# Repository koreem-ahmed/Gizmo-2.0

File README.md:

# Gizmo 2.0
## Description
Gizmo 2.0 is generally a small desk robot that acts as an AI companion whose only mission is to interact with you, dance with you, and even brainstorm with you. Gizmo 2.0 can help you organize your thoughts, and he gives incredible answers for any questions you ask him. Also, he is provided with a mic for voice and music recognition. So, you can have a little party with him, and it has 2 servo motors that act as joints for his arms, which are mainly used for dancing and interaction with his owner.

Gizmo was made after a lot of research and thinking i had like a really long time seeing totorial and example on the internet to see how to make a moving AI companian and which MCU to get and what could be its abailities so i used ESP32-S3 as the main MCU, inmp441 as a microphone, a speaker, 2 servo motors and a customed PCB to hold every thing together.

## Why it was biult
I had a really good time designing Gizmo as I made a unique 3D design with inspiration from EVE in the Wall-E robot film. As a kid I loved this character so much, and since it was really quiet and charming, it was like a new technology on earth to clean the planet, but I made it a little different. I made it to be like a moving thing on my desk to dance with me and interact with me when having long programming or designing sessions. Gizmo will be there for you. I wanted to make it with a moving wheels but i couldn't get a good design as well as that my desk is not that big for a moving robot So i ended up by making a static one with moving arms and a big processer which is the ESP32-S3.

There is another good reaseon for building Gizmo which is the amount of memories and thoughsts i gave into biulding it. Since this is my last project before attendign fallout which is a hackathon organized by Hack Club in shenzhen and i can't wait to go.

## How to use it / Build it
The first step of constructing Gizmo 2.0 is fabricating the PCB since it will be one of the main parts of the prototype. Also, you need it since the prototype doesn't have any additional space to maintain the electronics without the PCB. So, after fabricating the PCB, you should buy the components as well as jumpers and long wires for the LCD, speaker, and servo motors. After that you should 3D print the parts I provided in the repo, and for each part there is a compatible part in the main body, which will hold everything from servo motors to the connector and the head, which is part 5 or head connector; this connects to the neck of the head part.

Now we start the assembly. First of all, get your LCD and glue it to the front head part, then glue the speaker to the back head part, and assemble the 2 parts using the neck I provided, which has a place to hold all these parts together. After this, get the base and add the PCB after assembling everything and uploading the firmware. and close the base with the top part of the base and then assemble the main body and the servo motor holder and glue the servo motors to the part, then glue the arm to the servo motor after it to the main body after assembling the arms to the body. Now you have a full working prototype.

## CAD
I made this 3D design using onshape software, it was like a new experience for me to design a small prototype like a robot with this components so i had a new experience and i made every thing with smth like joints to hold it together. Also i added my name and HC for Hack Club.
And this is the design link:
https://cad.onshape.com/documents/7c9149f39106583a98e32532/w/5ca8de735c404b6ef83d1411/e/55ea2a7bab61e22144a448e0?renderMode=0&uiState=6a34a954f7594a7258307f8a
<br>

## Schematic
This is a simple diagram for my circiut it havethenamea small introduction a digra for whot will the system work and 2 systems the power and the ESP32-S3 connections

## PCB design
A polished PCB design with a copper filled zone to my GND net also i assimblied it many times until i got this one with no problems.

## Magazine

## BOM

| Item | Price | Quan. | Place | Link |
| :--- | :---: | :---: | :--- | :--- |
| ESP32-s3 | 10.55 | 1 | future electronics | [View Item](https://store.fut-electronics.com/products/esp32-s3-devkitc-1?srsltid=AfmBOoo5ok_RH336v4kgNkFmU0aAF1dDe45BG5KH02IJx1Rra65h0LNp) |
| ESP32 Camera OV5640 | 7.58 | 1 | makers | [View Item](https://makerselectronics.com/product/banana-pi-camera-ov5640-160-degree-5mp/?srsltid=AfmBOoqwwII_0DwU1h8Btitem8w31jUf-n4unO7NtXqaaZ5AVWlHgDsY) |
| 18650 Lithium Ion Rechargeable | 4.62 | 2 | future electronics | [View Item](https://fut-electronics.com) |
| AMS1117 3.3V Step-Down | 1 | 1 | micro ohm | [View Item](https://microohm-eg.com/ams1117-3-3-ldo-800ma-dc-5v-to-3-3v-step-down-power-supply-module/) |
| Step Down 5A XL4015 | 1.63 | 1 | micro ohm | [View Item](https://microohm-eg.com/dc-dc-step-down-converter-variable-5a-xl4015/) |
| BMS 2S 13A Lithium Battery Protection Board | 1.5 | 1 | micro ohm | [View Item](https://microohm-eg.com/2s-13a-18650-7-4v-8-4v-lithium-battery-protection-board/?utm_source=chatgpt.com) |
| 2S 8.4V 2A 18650 Lithium Battery Charger Module USB Type C | | 1 | ram electronics | [View Item](https://www.ram-e-shop.com/ar/shop/kit-li-2s-charger-2s-8-4v-2a-18650-lithium-battery-charger-module-usb-type-c-9295?srsltid=AfmBOoqNP3OFFPA_uS9me429NkSkgtTsNjoG1qEyEM67Y3l1D3-WlItv) |
| inm441 | 5.25 | 1 | Ali express | [View Item](https://ar.aliexpress.com/item/32934187800.html?gatewayAdapt=glo2ara) |
| i2s amplifier (max 98357) | 2.6 | 1 | future electronics | [View Item](https://store.fut-electronics.com/products/max98357-i2s-3w-class-d-amplifier-audio-decoder-module?srsltid=AfmBOoqAc6RcUHtToGTEkW9skKCJ9fX_xuc7YFtfUabfdsT7n0q2HLyD) |
| Speaker - 3W 4 Ohm | 1.54 | 1 | future electronics | [View Item](https://store.fut-electronics.com/products/speaker-3w-4-ohm?srsltid=AfmBOopv4otZbRL29DhJ3REfWfF-85G6EDgruAXGc6kVUNDOp2_l61lA) |
| LCD Module 1.28 inch Round Display | 9 | 1 | micro ohm | [View Item](https://microohm-eg.com/round-lcd-module-1-28-inch-240x240-ips-color-with-gc9a01-controller/) |
| TTP223 Capacitive Touch Sensor | 0.29 | 2 | makers | [View Item](https://makerselectronics.com/product/ttp223-capacitive-touch-sensor-module/?srsltid=AfmBOop7F_AzNeOoilzYLkXKq8DPKwVegbdnGAW85MecGYuK8TcNj0Ez) |
| 1.3 kg.cm servo | 2 | 2 | Circuits electronics | [View Item](https://circuits-elec.com/products/servo-motor-1-3-kg-cm-standard?srsltid=AfmBOoorhdeY6_q4NXN0ngcBwieEeBY9QWrYb_PrgZwciAxm65uJPD-Y) |
| PCB fabrication | 5 | 1 | JLCPCB | |
| 3D design | 20 | | | |
| **Total** | **75** | | | |

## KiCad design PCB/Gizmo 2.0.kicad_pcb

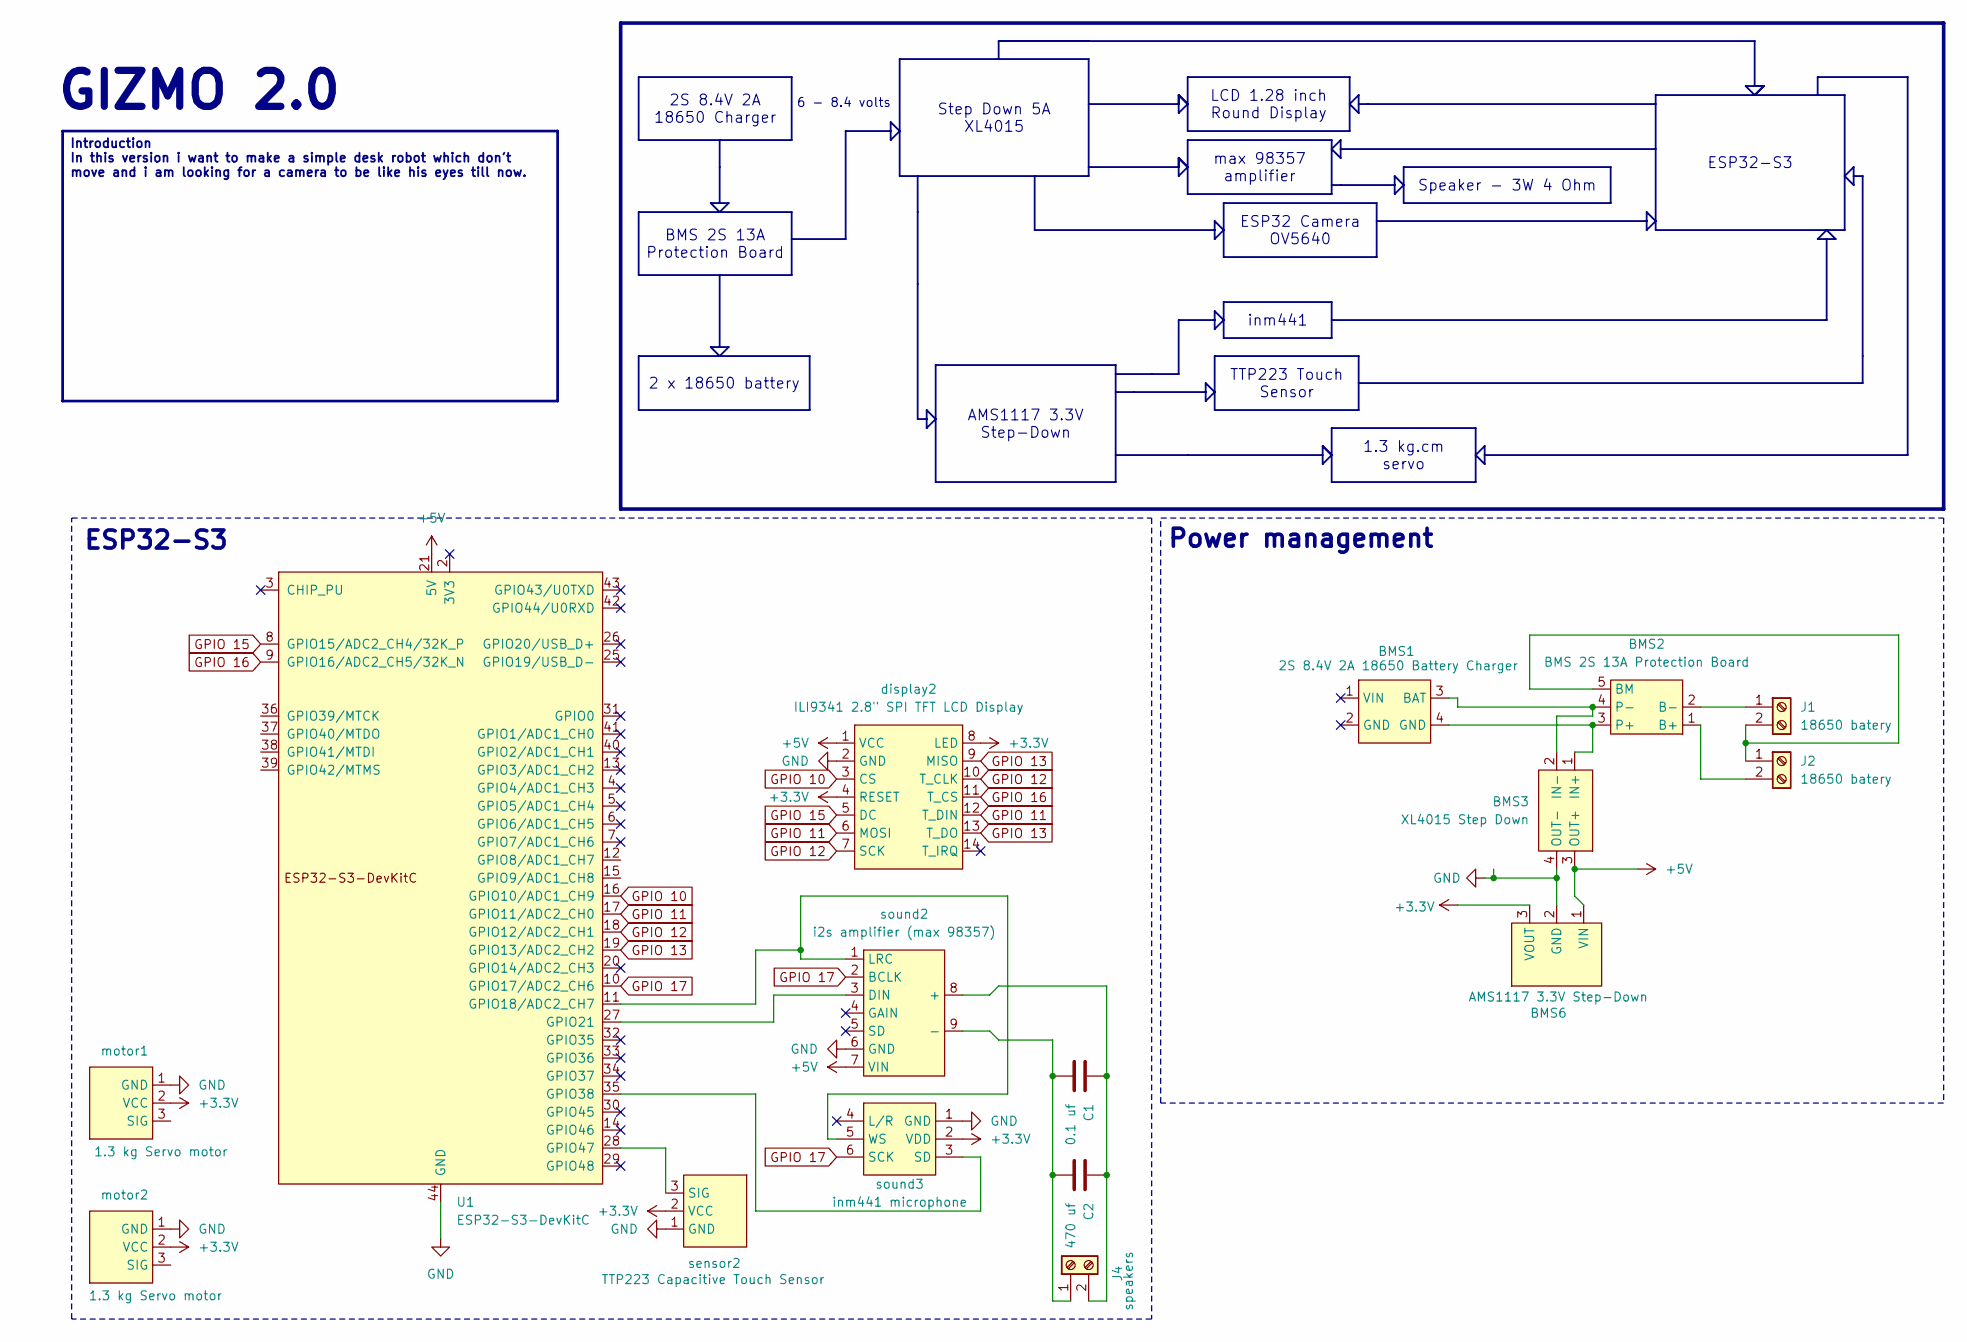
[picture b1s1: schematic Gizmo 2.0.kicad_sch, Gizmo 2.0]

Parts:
BMS1: 2S 8.4V 2A 18650 Battery Charger; TerminalBlock_4Ucon_1x04_P3.50mm_Horizontal
BMS2: BMS 2S 13A Protection Board; TerminalBlock_MetzConnect_Type059_RT06305HBWC_1x05_P3.50mm_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
BMS3: XL4015 Step Down; TerminalBlock_4Ucon_1x04_P3.50mm_Horizontal
BMS6: AMS1117 3.3V Step-Down; PinHeader_1x03_P2.54mm_Vertical
C1: 0.1 uf; CP_Radial_D5.0mm_P2.50mm
C2: 470 uf; CP_Radial_D6.3mm_P2.50mm
J1, J2: 18650 batery; PinHeader_1x02_P2.54mm_Vertical
J4: speakers; PinHeader_1x02_P2.54mm_Vertical
U1: ESP32-S3-DevKitC
display2: ILI9341 2.8" SPI TFT LCD Display; ILI9341 SPI display
motor1, motor2: 1.3 kg Servo motor; PinSocket_1x03_P2.54mm_Vertical
sensor2: TTP223 Capacitive Touch Sensor; PinSocket_1x03_P2.54mm_Vertical
sound2: i2s amplifier (max 98357); max 98357 i2s amplifier
sound3: inm441 microphone; inm441 Speaker

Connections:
+3.3V: BMS6.3 (VOUT), display2.4 (RESET), display2.8 (LED), motor1.2 (VCC), motor2.2 (VCC), sensor2.2 (VCC), sound3.2 (VDD)
+5V: BMS3.3 (OUT+), BMS6.1 (VIN), U1.21 (5V), display2.1 (VCC), sound2.7 (VIN)
GND: BMS3.4 (OUT-), BMS6.2 (GND), U1.22 (GND), U1.23 (GND), U1.24 (GND), U1.44 (GND), display2.2 (GND), motor1.1 (GND), motor2.1 (GND), sensor2.1 (GND), sound2.6 (GND), sound3.1 (GND)
GPIO 10: U1.16 (GPIO10/ADC1_CH9), display2.3 (CS)
GPIO 11: U1.17 (GPIO11/ADC2_CH0), display2.6 (MOSI), display2.12 (T_DIN)
GPIO 12: U1.18 (GPIO12/ADC2_CH1), display2.7 (SCK), display2.10 (T_CLK)
GPIO 13: U1.19 (GPIO13/ADC2_CH2), display2.9 (MISO), display2.13 (T_DO)
GPIO 15: U1.8 (GPIO15/ADC2_CH4/32K_P), display2.5 (DC)
GPIO 16: U1.9 (GPIO16/ADC2_CH5/32K_N), display2.11 (T_CS)
GPIO 17: U1.10 (GPIO17/ADC2_CH6), sound2.2 (BCLK), sound3.6 (SCK)
unnamed: BMS1.3 (BAT), BMS2.4 (P-), BMS3.2 (IN-)
unnamed: BMS2.1 (B+), J2.2
unnamed: BMS2.2 (B-), J1.1
unnamed: BMS2.5 (BM), J1.2, J2.1
unnamed: BMS1.4 (GND), BMS2.3 (P+), BMS3.1 (IN+)
unnamed: C1.2, C2.2, J4.1, sound2.9 (-)
unnamed: C1.1, C2.1, J4.2, sound2.8 (+)
unnamed: U1.11 (GPIO18/ADC2_CH7), sound2.1 (LRC), sound3.5 (WS)
unnamed: U1.27 (GPIO21), sound2.3 (DIN)
unnamed: U1.35 (GPIO38), sound3.3 (SD)
unnamed: U1.28 (GPIO47), sensor2.3 (SIG)

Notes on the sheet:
6 - 8.4 volts
GIZMO 2.0
ESP32-S3
Power management
2 x 18650 battery
LCD 1.28 inch Round Display
inm441
max 98357 amplifier
AMS1117 3.3V Step-Down
Speaker - 3W 4 Ohm
ESP32 Camera OV5640
1.3 kg.cm servo
Introduction In this version i want to make a simple desk robot which don't move and i am looking for a camera to be like his eyes till now.
TTP223 Touch Sensor
2S 8.4V 2A 18650 Charger
BMS 2S 13A Protection Board
Step Down 5A XL4015

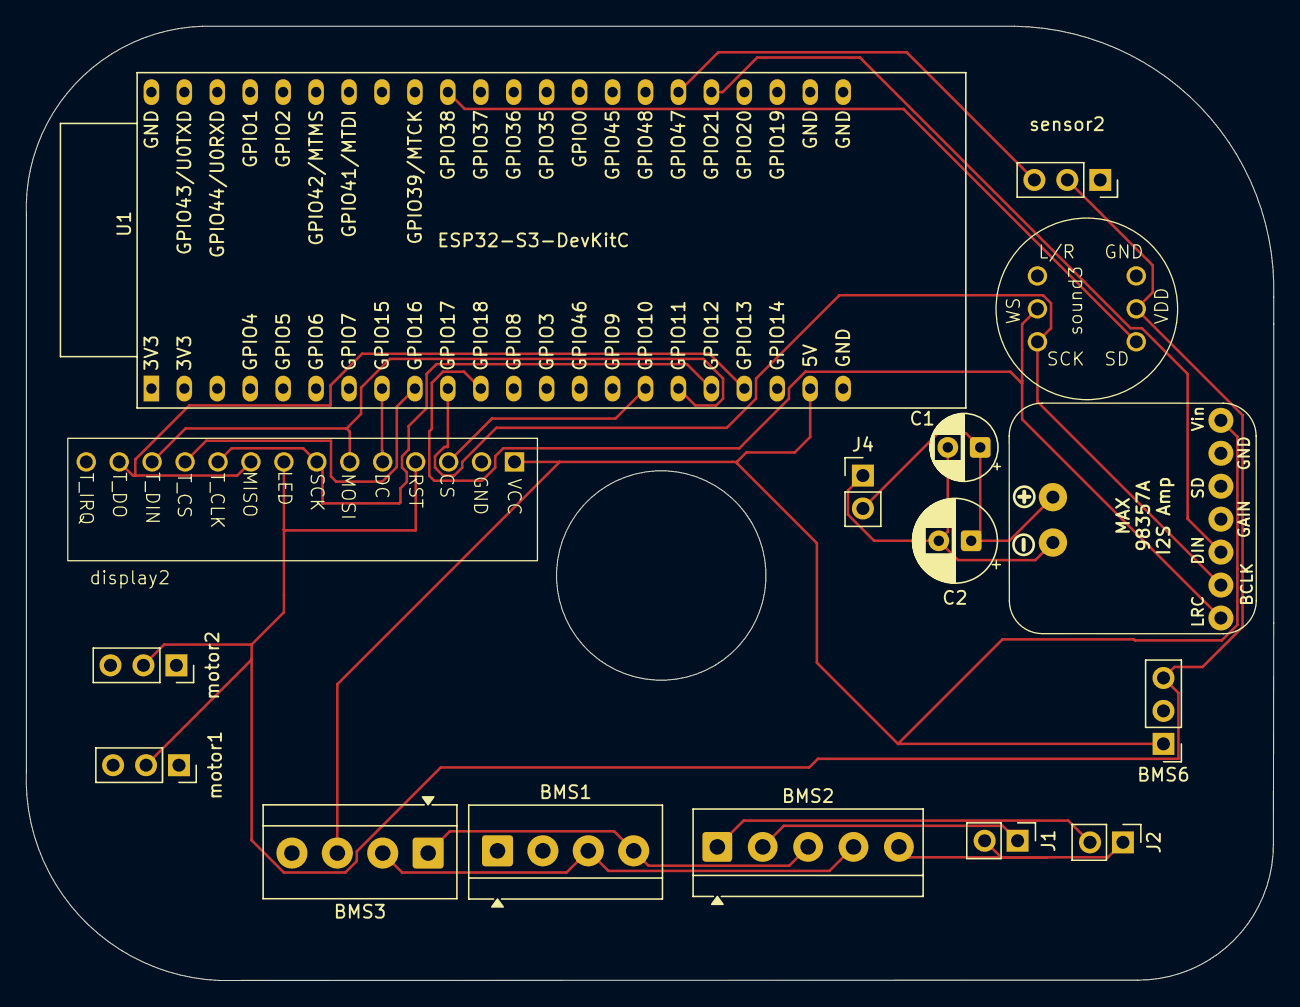
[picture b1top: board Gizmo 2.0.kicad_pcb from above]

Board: 2 copper layers, 96.2 x 73.6 mm, 16 parts (0 on the bottom side), 21 nets.

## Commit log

2026-06-19 Add description for Gizmo 2.0
    Added a description section to the README.
2026-06-19 Revise README for Gizmo 2.0 with detailed descriptions
    Updated the README to improve clarity and detail about Gizmo 2.0's features, design inspiration, and assembly instructions.
2026-06-19 Add resource links to code.md
    Added references and resources for using the repository.
2026-06-19 Fix section header formatting in README.md
2026-06-19 Update code.md with project details and plans
    Clarified the purpose of the firmware and future plans for development.
2026-06-24 Update BOM.csv with new quantities and totals
2026-06-24 Add BOM section with item details and prices
